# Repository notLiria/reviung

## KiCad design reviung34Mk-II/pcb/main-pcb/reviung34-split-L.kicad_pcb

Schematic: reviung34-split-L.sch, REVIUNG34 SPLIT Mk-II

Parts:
D1, D2, D3, D4, D5, D6, D7, D8, D9, D10, D11, D12, D13, D14, D15, D16, D17, D18, D19, D20, D21, D22, D23, D24, D25, D26, D27, D28, D29, D30, D31, D32, D33, D34: 1N4148; D3_TH_SMD_1side
H1: MountingHole_Pad; MountingHole_4.3mm_M4_ISO7380_Pad
J1, J2: 8P8C; RJ45-DS1128-05-S8B8P
RESET1: SW_PUSH; ResetSW_1side
SW1, SW2, SW3, SW4, SW5, SW6, SW7, SW8, SW9, SW10, SW11, SW12, SW13, SW14, SW15, SW16, SW17, SW18, SW19, SW20, SW21, SW22, SW23, SW24, SW25, SW26, SW27, SW28, SW29, SW30, SW31, SW32, SW33, SW34, SW35: SW_PUSH; CherryMX_Hotswap
U1: ProMicro_r; ProMicro

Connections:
unnamed: D1.2, SW1.2
unnamed: D2.2, SW2.2
unnamed: D3.2, SW3.2
unnamed: D4.2, SW4.2
unnamed: D5.2, SW5.2
unnamed: D6.2, SW6.2
unnamed: D7.2, SW7.2
unnamed: D8.2, SW8.2
unnamed: D9.2, SW9.2
unnamed: D10.2, SW10.2
unnamed: D11.2, SW11.2
unnamed: D12.2, SW12.2
unnamed: D13.2, SW13.2
unnamed: D14.2, SW14.2
unnamed: D15.2, SW15.2
unnamed: D16.2, SW16.2
unnamed: D17.2, SW17.2
unnamed: D18.2, SW18.2, SW35.2
unnamed: D19.2, SW19.2
unnamed: D20.2, SW20.2
unnamed: D21.2, SW21.2
unnamed: D22.2, SW22.2
unnamed: D23.2, SW23.2
unnamed: D24.2, SW24.2
unnamed: D25.2, SW25.2
unnamed: D26.2, SW26.2
unnamed: D27.2, SW27.2
unnamed: D28.2, SW28.2
unnamed: D29.2, SW29.2
unnamed: D30.2, SW30.2
unnamed: D31.2, SW31.2
unnamed: D32.2, SW32.2
unnamed: D33.2, SW33.2
unnamed: D34.2, SW34.2
VCC: U1.21 (VCC)
col0: SW1.1, SW6.1, SW11.1, U1.7 (D4/4)
col1: SW2.1, SW7.1, SW12.1, U1.8 (C6/5)
col2: SW3.1, SW8.1, SW13.1, SW16.1, U1.9 (D7/6)
col3: SW4.1, SW9.1, SW14.1, SW17.1, U1.10 (E6/7)
col4: SW5.1, SW10.1, SW15.1, SW18.1, SW35.1, U1.11 (B4/8)
col5: J1.5, U1.16 (15/B1)
col6: J1.6, U1.15 (14/B3)
col7: J1.7, U1.14 (16/B2)
col8: J1.8, U1.13 (10/B6)
col15: J2.5, SW19.1, SW23.1, SW27.1, SW31.1
col16: J2.6, SW20.1, SW24.1, SW28.1, SW32.1
col17: J2.7, SW21.1, SW25.1, SW29.1, SW33.1
col18: J2.8, SW22.1, SW26.1, SW30.1, SW34.1
reset: RESET1.1, U1.22 (RST)
row0: D1.1, D2.1, D3.1, D4.1, D5.1, J1.1, U1.20 (A3/F4)
row1: D6.1, D7.1, D8.1, D9.1, D10.1, J1.2, U1.19 (A2/F5)
row2: D11.1, D12.1, D13.1, D14.1, D15.1, J1.3, U1.18 (A1/F6)
row3: D16.1, D17.1, D18.1, J1.4, U1.17 (A0/F7)
row10: D19.1, D20.1, D21.1, D22.1, J2.1
row11: D23.1, D24.1, D25.1, D26.1, J2.2
row12: D27.1, D28.1, D29.1, D30.1, J2.3
row13: D31.1, D32.1, D33.1, D34.1, J2.4

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
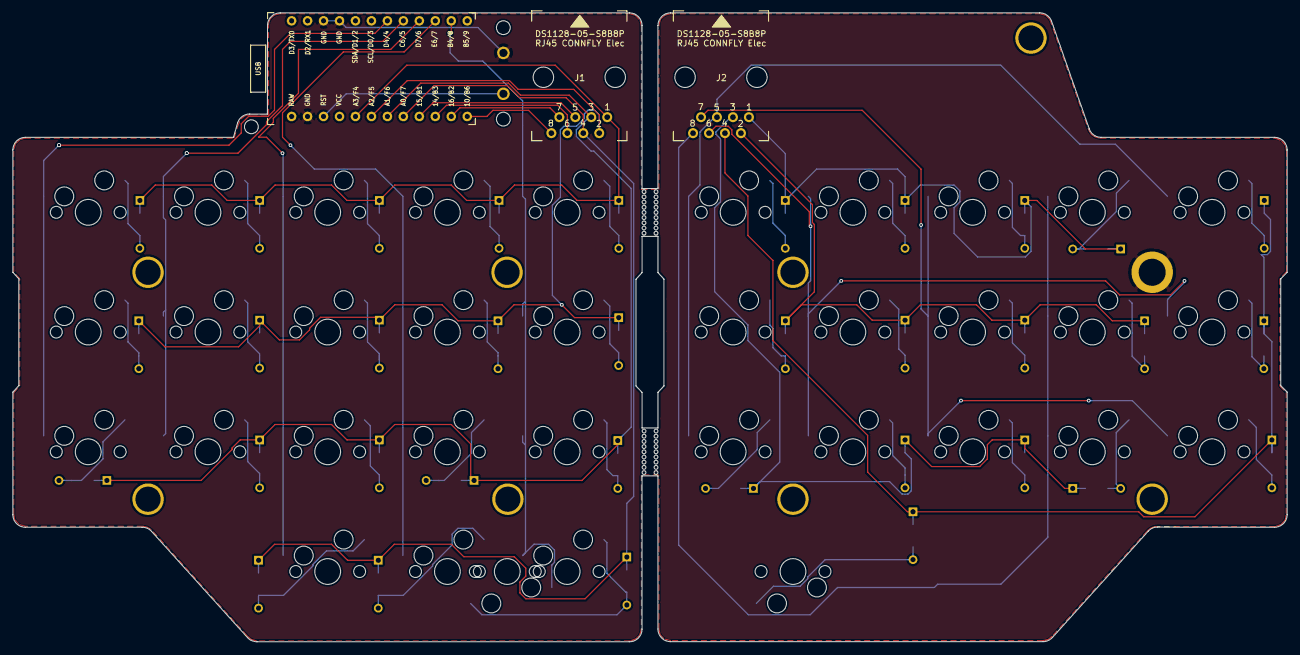
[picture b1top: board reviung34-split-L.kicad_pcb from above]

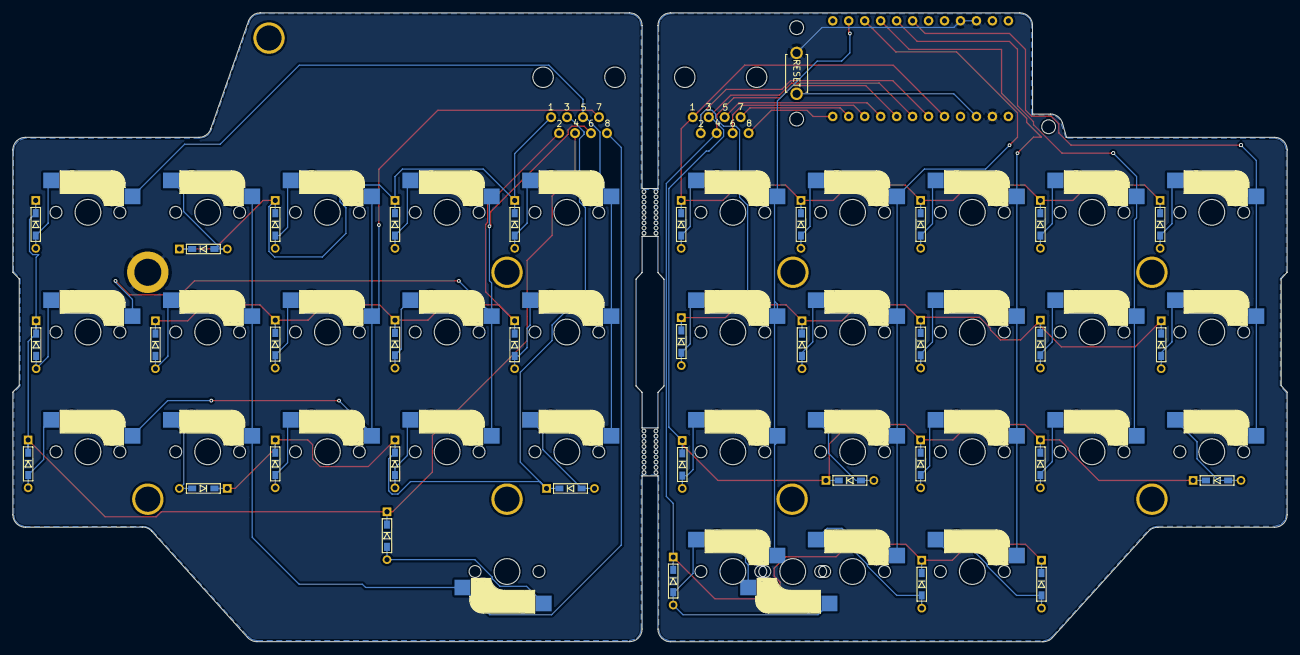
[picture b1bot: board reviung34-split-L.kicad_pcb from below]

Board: 2 copper layers, 202.7 x 100.1 mm, 89 parts (35 on the bottom side), 57 nets.

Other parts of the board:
H1#2: MountingHole_Pad; MountingHole_4.3mm_M4_ISO7380_Pad
H2: H2; M2_Hole_TH_Outside
H3: H3; M2_Hole_TH_Outside
H4: H4; M2_Hole_TH_Outside
H5: H5; HOLE_2.2mm
H6: H6; MountingHole_2.2mm_M2_ISO7380
H7: H7; HOLE_2.2mm
H8: H8; M2_Hole_TH_Outside
H9: H9; M2_Hole_TH_Outside
H10: H10; M2_Hole_TH_Outside
H12: H12; M2_Hole_TH_Outside
breakaway: Stamp_Holes_7.5mm
breakaway#2, breakaway#3, breakaway#4: Stamp_Holes_7.5mm

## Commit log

2021-02-14 Modified to use Kailh hotswaps
